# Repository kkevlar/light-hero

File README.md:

# light-hero

Fun work is in justin.c

`make rundemo`

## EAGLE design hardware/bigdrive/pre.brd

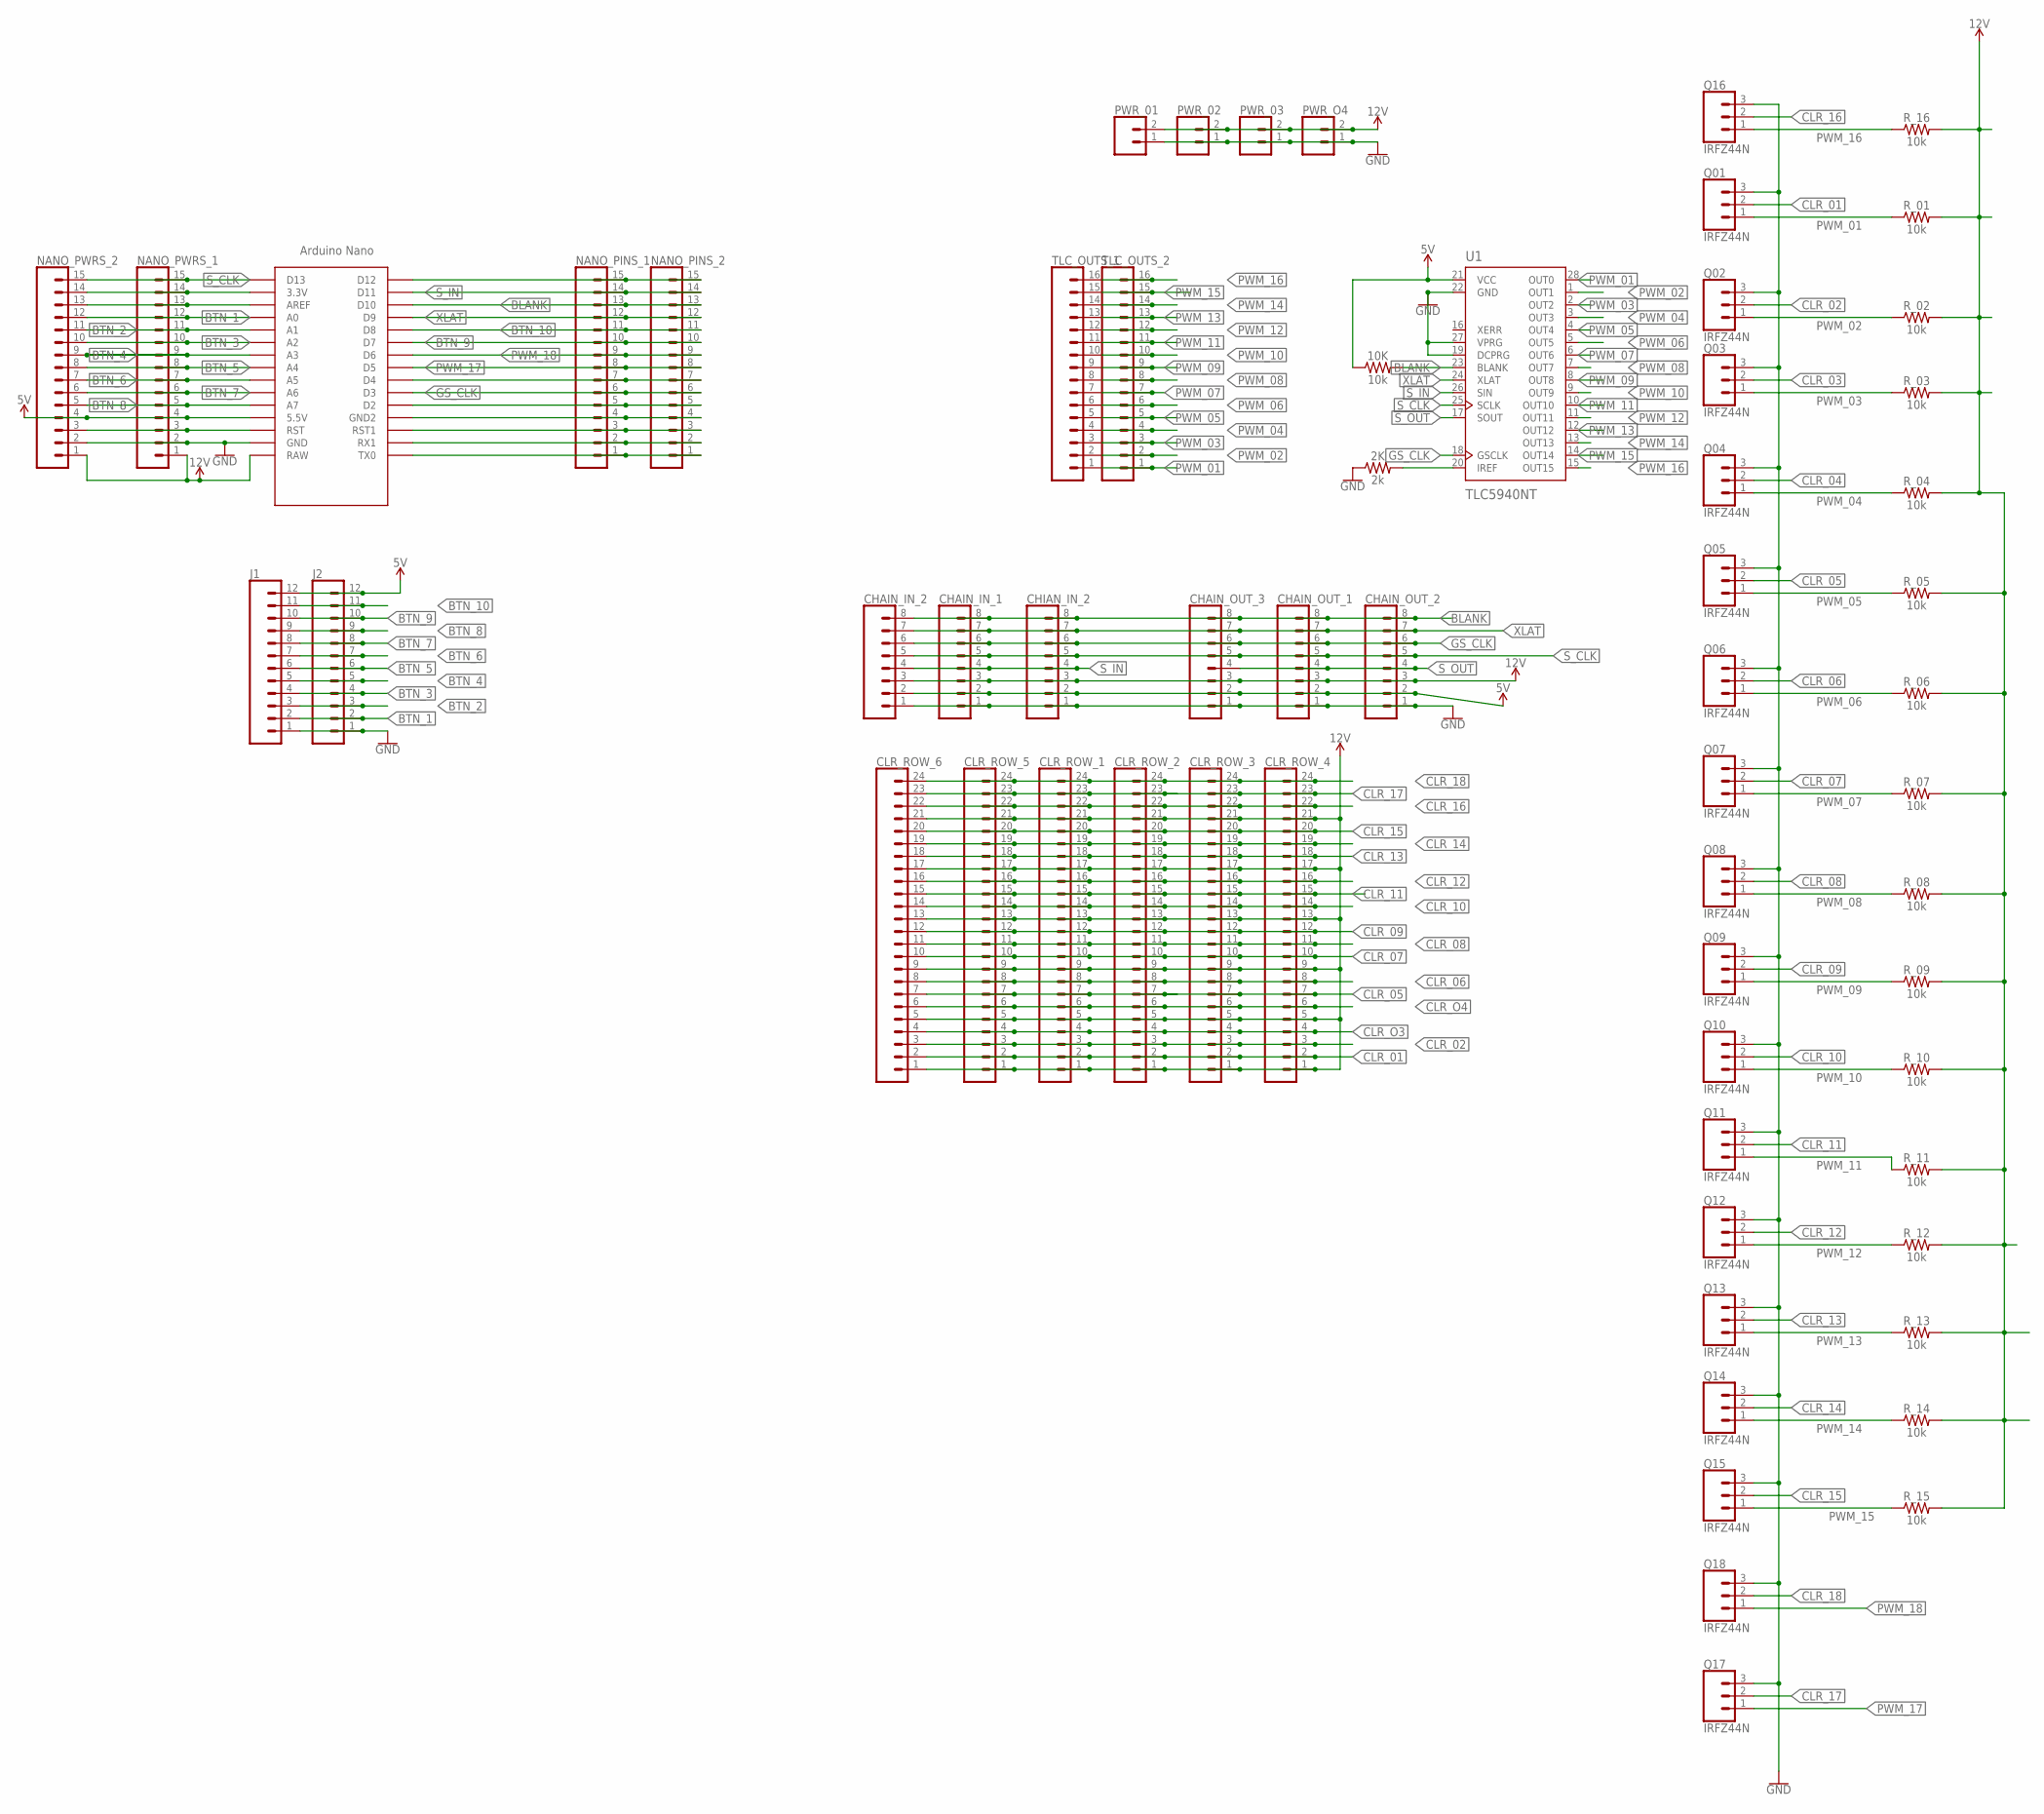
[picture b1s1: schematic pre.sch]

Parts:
2K: 2k; AXIAL-0.3
10K: 10k; AXIAL-0.3
CHAIN_IN_1, CHAIN_IN_2: CONN_08"; 1X08
CHAIN_OUT_1, CHAIN_OUT_2, CHAIN_OUT_3: CONN_08"; 1X08
CHIAN_IN_2: CONN_08"; 1X08
CLR_ROW_1, CLR_ROW_2, CLR_ROW_3, CLR_ROW_4, CLR_ROW_5, CLR_ROW_6: CONN_24; 1X24
J1, J2: CONN_12; 1X12
NANO_PINS_1, NANO_PINS_2: CONN_15; 1X15
NANO_PWRS_1, NANO_PWRS_2: CONN_15; 1X15
PWR_01, PWR_02: CONN_023.5MM; SCREWTERMINAL-3.5MM-2
PWR_03: CONN_02; 1X02
PWR_O4: CONN_02; 1X02
Q01, Q02, Q03, Q04, Q05, Q06, Q07, Q08, Q09, Q10, Q11, Q12, Q13, Q14, Q15, Q16, Q17, Q18: IRFZ44N; 1X03
R_01, R_02, R_03, R_04, R_05, R_06, R_07, R_08, R_09, R_10, R_11, R_12, R_13, R_14, R_15, R_16: 10k; AXIAL-0.3
TLC_OUTS_1, TLC_OUTS_2: CONN_16; 1X16
U1: TLC5940NT; DIL28-3
U$1: NANO

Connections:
5V: 10K.P$1 (1), CHAIN_IN_1.2, CHAIN_IN_2.2, CHAIN_OUT_1.2, CHAIN_OUT_2.2, CHAIN_OUT_3.2, CHIAN_IN_2.2, J1.12, J2.12, NANO_PWRS_1.4, NANO_PWRS_2.4, U1.21 (VCC), U$1.5V (5.5V)
12V: CHAIN_IN_1.3, CHAIN_IN_2.3, CHAIN_OUT_1.3, CHAIN_OUT_2.3, CHAIN_OUT_3.3, CHIAN_IN_2.3, CLR_ROW_1.1, CLR_ROW_1.5, CLR_ROW_1.9, CLR_ROW_1.13, CLR_ROW_1.17, CLR_ROW_1.21, CLR_ROW_2.1, CLR_ROW_2.5, CLR_ROW_2.9, CLR_ROW_2.13, CLR_ROW_2.17, CLR_ROW_2.21, CLR_ROW_3.1, CLR_ROW_3.5, CLR_ROW_3.9, CLR_ROW_3.13, CLR_ROW_3.17, CLR_ROW_3.21, CLR_ROW_4.1, CLR_ROW_4.5, CLR_ROW_4.9, CLR_ROW_4.13, CLR_ROW_4.17, CLR_ROW_4.21, CLR_ROW_5.1, CLR_ROW_5.5, CLR_ROW_5.9, CLR_ROW_5.13, CLR_ROW_5.17, CLR_ROW_5.21, CLR_ROW_6.1, CLR_ROW_6.5, CLR_ROW_6.9, CLR_ROW_6.13, CLR_ROW_6.17, CLR_ROW_6.21, NANO_PWRS_1.1, NANO_PWRS_2.1, PWR_01.2, PWR_02.2, PWR_03.2, PWR_O4.2, R_01.P$2 (2), R_02.P$2 (2), R_03.P$2 (2), R_04.P$2 (2), R_05.P$2 (2), R_06.P$2 (2), R_07.P$2 (2), R_08.P$2 (2), R_09.P$2 (2), R_10.P$2 (2), R_11.P$2 (2), R_12.P$2 (2), R_13.P$2 (2), R_14.P$2 (2), R_15.P$2 (2), R_16.P$2 (2), U$1.RAW
BLANK: 10K.P$2 (2), CHAIN_IN_1.8, CHAIN_IN_2.8, CHAIN_OUT_1.8, CHAIN_OUT_2.8, CHAIN_OUT_3.8, CHIAN_IN_2.8, NANO_PINS_1.13, NANO_PINS_2.13, U1.23 (BLANK), U$1.D10
BTN_1: J1.2, J2.2, NANO_PWRS_1.12, NANO_PWRS_2.12, U$1.A0
BTN_2: J1.3, J2.3, NANO_PWRS_1.11, NANO_PWRS_2.11, U$1.A1
BTN_3: J1.4, J2.4, NANO_PWRS_1.10, NANO_PWRS_2.10, U$1.A2
BTN_4: J1.5, J2.5, NANO_PWRS_1.9, NANO_PWRS_2.9, U$1.A3
BTN_5: J1.6, J2.6, NANO_PWRS_1.8, NANO_PWRS_2.8, U$1.A4
BTN_6: J1.7, J2.7, NANO_PWRS_1.7, NANO_PWRS_2.7, U$1.A5
BTN_7: J1.8, J2.8, NANO_PWRS_1.6, NANO_PWRS_2.6, U$1.A6
BTN_8: J1.9, J2.9, NANO_PWRS_1.5, NANO_PWRS_2.5, U$1.A7
BTN_9: J1.10, J2.10, NANO_PINS_1.10, NANO_PINS_2.10, U$1.D7
BTN_10: J1.11, J2.11, NANO_PINS_1.11, NANO_PINS_2.11, U$1.D8
CLR_01: CLR_ROW_1.2, CLR_ROW_2.2, CLR_ROW_3.2, CLR_ROW_4.2, CLR_ROW_5.2, CLR_ROW_6.2, Q01.2
CLR_02: CLR_ROW_1.3, CLR_ROW_2.3, CLR_ROW_3.3, CLR_ROW_4.3, CLR_ROW_5.3, CLR_ROW_6.3, Q02.2
CLR_03: Q03.2
CLR_04: Q04.2
CLR_05: CLR_ROW_1.7, CLR_ROW_2.7, CLR_ROW_3.7, CLR_ROW_4.7, CLR_ROW_5.7, CLR_ROW_6.7, Q05.2
CLR_06: CLR_ROW_1.8, CLR_ROW_2.8, CLR_ROW_3.8, CLR_ROW_4.8, CLR_ROW_5.8, CLR_ROW_6.8, Q06.2
CLR_07: CLR_ROW_1.10, CLR_ROW_2.10, CLR_ROW_3.10, CLR_ROW_4.10, CLR_ROW_5.10, CLR_ROW_6.10, Q07.2
CLR_08: CLR_ROW_1.11, CLR_ROW_2.11, CLR_ROW_3.11, CLR_ROW_4.11, CLR_ROW_5.11, CLR_ROW_6.11, Q08.2
CLR_09: CLR_ROW_1.12, CLR_ROW_2.12, CLR_ROW_3.12, CLR_ROW_4.12, CLR_ROW_5.12, CLR_ROW_6.12, Q09.2
CLR_10: CLR_ROW_1.14, CLR_ROW_2.14, CLR_ROW_3.14, CLR_ROW_4.14, CLR_ROW_5.14, CLR_ROW_6.14, Q10.2
CLR_11: CLR_ROW_1.15, CLR_ROW_2.15, CLR_ROW_3.15, CLR_ROW_4.15, CLR_ROW_5.15, CLR_ROW_6.15, Q11.2
CLR_12: CLR_ROW_1.16, CLR_ROW_2.16, CLR_ROW_3.16, CLR_ROW_4.16, CLR_ROW_5.16, CLR_ROW_6.16, Q12.2
CLR_13: CLR_ROW_1.18, CLR_ROW_2.18, CLR_ROW_3.18, CLR_ROW_4.18, CLR_ROW_5.18, CLR_ROW_6.18, Q13.2
CLR_14: CLR_ROW_1.19, CLR_ROW_2.19, CLR_ROW_3.19, CLR_ROW_4.19, CLR_ROW_5.19, CLR_ROW_6.19, Q14.2
CLR_15: CLR_ROW_1.20, CLR_ROW_2.20, CLR_ROW_3.20, CLR_ROW_4.20, CLR_ROW_5.20, CLR_ROW_6.20, Q15.2
CLR_16: CLR_ROW_1.22, CLR_ROW_2.22, CLR_ROW_3.22, CLR_ROW_4.22, CLR_ROW_5.22, CLR_ROW_6.22, Q16.2
CLR_17: CLR_ROW_1.23, CLR_ROW_2.23, CLR_ROW_3.23, CLR_ROW_4.23, CLR_ROW_5.23, CLR_ROW_6.23, Q17.2
CLR_18: CLR_ROW_1.24, CLR_ROW_2.24, CLR_ROW_3.24, CLR_ROW_4.24, CLR_ROW_5.24, CLR_ROW_6.24, Q18.2
CLR_O3: CLR_ROW_1.4, CLR_ROW_2.4, CLR_ROW_3.4, CLR_ROW_4.4, CLR_ROW_5.4, CLR_ROW_6.4
CLR_O4: CLR_ROW_1.6, CLR_ROW_2.6, CLR_ROW_3.6, CLR_ROW_4.6, CLR_ROW_5.6, CLR_ROW_6.6
GND: 2K.P$1 (1), CHAIN_IN_1.1, CHAIN_IN_2.1, CHAIN_OUT_1.1, CHAIN_OUT_2.1, CHAIN_OUT_3.1, CHIAN_IN_2.1, J1.1, J2.1, NANO_PINS_1.4, NANO_PINS_2.4, NANO_PWRS_1.2, NANO_PWRS_2.2, PWR_01.1, PWR_02.1, PWR_03.1, PWR_O4.1, Q01.3, Q02.3, Q03.3, Q04.3, Q05.3, Q06.3, Q07.3, Q08.3, Q09.3, Q10.3, Q11.3, Q12.3, Q13.3, Q14.3, Q15.3, Q16.3, Q17.3, Q18.3, U1.19 (DCPRG), U1.22 (GND), U1.27 (VPRG), U$1.GND, U$1.GND1 (GND2)
GS_CLK: CHAIN_IN_1.6, CHAIN_IN_2.6, CHAIN_OUT_1.6, CHAIN_OUT_2.6, CHAIN_OUT_3.6, CHIAN_IN_2.6, NANO_PINS_1.6, NANO_PINS_2.6, U1.18 (GSCLK), U$1.D3
unnamed: 2K.P$2 (2), U1.20 (IREF)
unnamed: NANO_PWRS_1.14, NANO_PWRS_2.14, U$1.3.3V
unnamed: NANO_PWRS_1.13, NANO_PWRS_2.13, U$1.AREF
unnamed: NANO_PWRS_1.3, NANO_PWRS_2.3, U$1.RST
unnamed: NANO_PINS_1.15, NANO_PINS_2.15, U$1.D12
unnamed: NANO_PINS_1.3, NANO_PINS_2.3, U$1.RST1
unnamed: NANO_PINS_1.2, NANO_PINS_2.2, U$1.RX1
unnamed: NANO_PINS_1.7, NANO_PINS_2.7, U$1.D4
unnamed: NANO_PINS_1.1, NANO_PINS_2.1, U$1.TX0
unnamed: NANO_PINS_1.5, NANO_PINS_2.5, U$1.D2
PWM_01: Q01.1, R_01.P$1 (1), TLC_OUTS_1.1, TLC_OUTS_2.1, U1.28 (OUT0)
PWM_02: Q02.1, R_02.P$1 (1), TLC_OUTS_1.2, TLC_OUTS_2.2, U1.1 (OUT1)
PWM_03: Q03.1, R_03.P$1 (1), TLC_OUTS_1.3, TLC_OUTS_2.3, U1.2 (OUT2)
PWM_04: Q04.1, R_04.P$1 (1), TLC_OUTS_1.4, TLC_OUTS_2.4, U1.3 (OUT3)
PWM_05: Q05.1, R_05.P$1 (1), TLC_OUTS_1.5, TLC_OUTS_2.5, U1.4 (OUT4)
PWM_06: Q06.1, R_06.P$1 (1), TLC_OUTS_1.6, TLC_OUTS_2.6, U1.5 (OUT5)
PWM_07: Q07.1, R_07.P$1 (1), TLC_OUTS_1.7, TLC_OUTS_2.7, U1.6 (OUT6)
PWM_08: Q08.1, R_08.P$1 (1), TLC_OUTS_1.8, TLC_OUTS_2.8, U1.7 (OUT7)
PWM_09: Q09.1, R_09.P$1 (1), TLC_OUTS_1.9, TLC_OUTS_2.9, U1.8 (OUT8)
PWM_10: Q10.1, R_10.P$1 (1), TLC_OUTS_1.10, TLC_OUTS_2.10, U1.9 (OUT9)
PWM_11: Q11.1, R_11.P$1 (1), TLC_OUTS_1.11, TLC_OUTS_2.11, U1.10 (OUT10)
PWM_12: Q12.1, R_12.P$1 (1), TLC_OUTS_1.12, TLC_OUTS_2.12, U1.11 (OUT11)
PWM_13: Q13.1, R_13.P$1 (1), TLC_OUTS_1.13, TLC_OUTS_2.13, U1.12 (OUT12)
PWM_14: Q14.1, R_14.P$1 (1), TLC_OUTS_1.14, TLC_OUTS_2.14, U1.13 (OUT13)
PWM_15: Q15.1, R_15.P$1 (1), TLC_OUTS_1.15, TLC_OUTS_2.15, U1.14 (OUT14)
PWM_16: Q16.1, R_16.P$1 (1), TLC_OUTS_1.16, TLC_OUTS_2.16, U1.15 (OUT15)
PWM_17: NANO_PINS_1.8, NANO_PINS_2.8, Q17.1, U$1.D5
PWM_18: NANO_PINS_1.9, NANO_PINS_2.9, Q18.1, U$1.D6
S_CLK: CHAIN_IN_1.5, CHAIN_IN_2.5, CHAIN_OUT_1.5, CHAIN_OUT_2.5, CHAIN_OUT_3.5, CHIAN_IN_2.5, NANO_PWRS_1.15, NANO_PWRS_2.15, U1.25 (SCLK), U$1.D13
S_IN: CHAIN_IN_1.4, CHAIN_IN_2.4, CHIAN_IN_2.4, NANO_PINS_1.14, NANO_PINS_2.14, U1.26 (SIN), U$1.D11
S_OUT: CHAIN_OUT_1.4, CHAIN_OUT_2.4, CHAIN_OUT_3.4, U1.17 (SOUT)
XLAT: CHAIN_IN_1.7, CHAIN_IN_2.7, CHAIN_OUT_1.7, CHAIN_OUT_2.7, CHAIN_OUT_3.7, CHIAN_IN_2.7, NANO_PINS_1.12, NANO_PINS_2.12, U1.24 (XLAT), U$1.D9

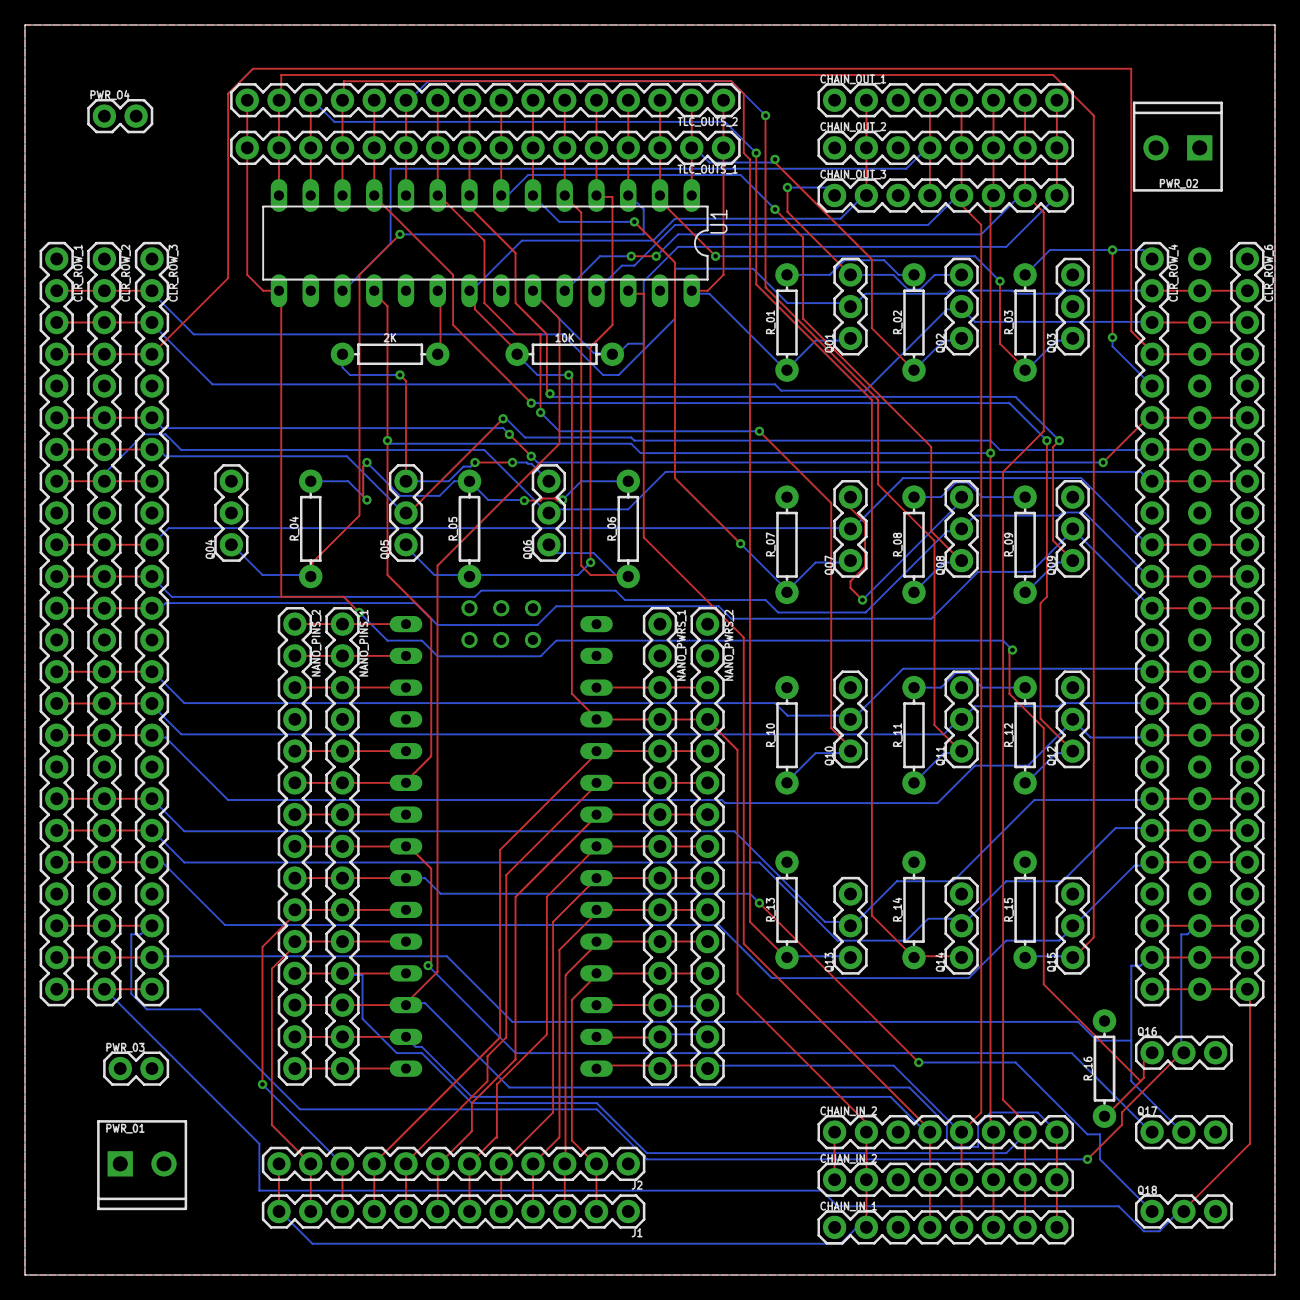
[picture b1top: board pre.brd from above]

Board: 2 copper layers, 100.0 x 100.0 mm, 62 parts (1 on the bottom side), 65 nets.

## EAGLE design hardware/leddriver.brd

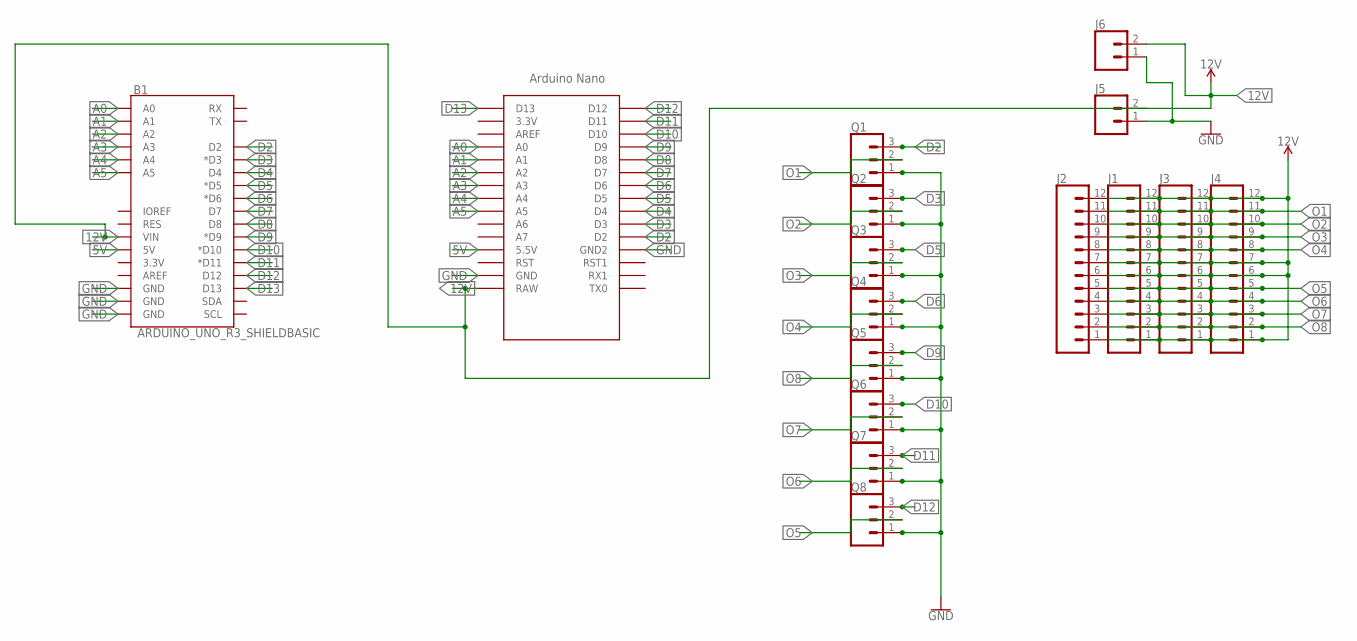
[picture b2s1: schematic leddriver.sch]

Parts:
B1: ARDUINO_UNO_R3_SHIELDBASIC; UNO_R3_SHIELD
J1, J2, J3, J4: CONN_12; 1X12
J5, J6: CONN_02; 1X02
Q1, Q2, Q3, Q4, Q5, Q6, Q7, Q8: 455-1750-1-ND; 1X03
U$1: NANO

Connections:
5V: B1.5V, U$1.5V (5.5V)
12V: B1.VIN, J1.1, J1.6, J1.7, J1.12, J2.1, J2.6, J2.7, J2.12, J3.1, J3.6, J3.7, J3.12, J4.1, J4.6, J4.7, J4.12, J5.2, J6.2, U$1.RAW
A0: B1.A0, U$1.A0
A1: B1.A1, U$1.A1
A2: B1.A2, U$1.A2
A3: B1.A3, U$1.A3
A4: B1.A4, U$1.A4
A5: B1.A5, U$1.A5
D2: B1.D2, Q1.3, U$1.D2
D3: B1.D3 (*D3), Q2.3, U$1.D3
D4: B1.D4, U$1.D4
D5: B1.D5 (*D5), Q3.3, U$1.D5
D6: B1.D6 (*D6), Q4.3, U$1.D6
D7: B1.D7, U$1.D7
D8: B1.D8, U$1.D8
D9: B1.D9 (*D9), Q5.3, U$1.D9
D10: B1.D10 (*D10), Q6.3, U$1.D10
D11: B1.D11 (*D11), Q7.3, U$1.D11
D12: B1.D12, Q8.3, U$1.D12
D13: B1.D13, U$1.D13
GND: B1.GND@0 (GND), B1.GND@1 (GND), B1.GND@2 (GND), J5.1, J6.1, Q1.1, Q2.1, Q3.1, Q4.1, Q5.1, Q6.1, Q7.1, Q8.1, U$1.GND, U$1.GND1 (GND2)
O1: J1.11, J2.11, J3.11, J4.11, Q1.2
O2: J1.10, J2.10, J3.10, J4.10, Q2.2
O3: J1.9, J2.9, J3.9, J4.9, Q3.2
O4: J1.8, J2.8, J3.8, J4.8, Q4.2
O5: J1.5, J2.5, J3.5, J4.5, Q8.2
O6: J1.4, J2.4, J3.4, J4.4, Q7.2
O7: J1.3, J2.3, J3.3, J4.3, Q6.2
O8: J1.2, J2.2, J3.2, J4.2, Q5.2

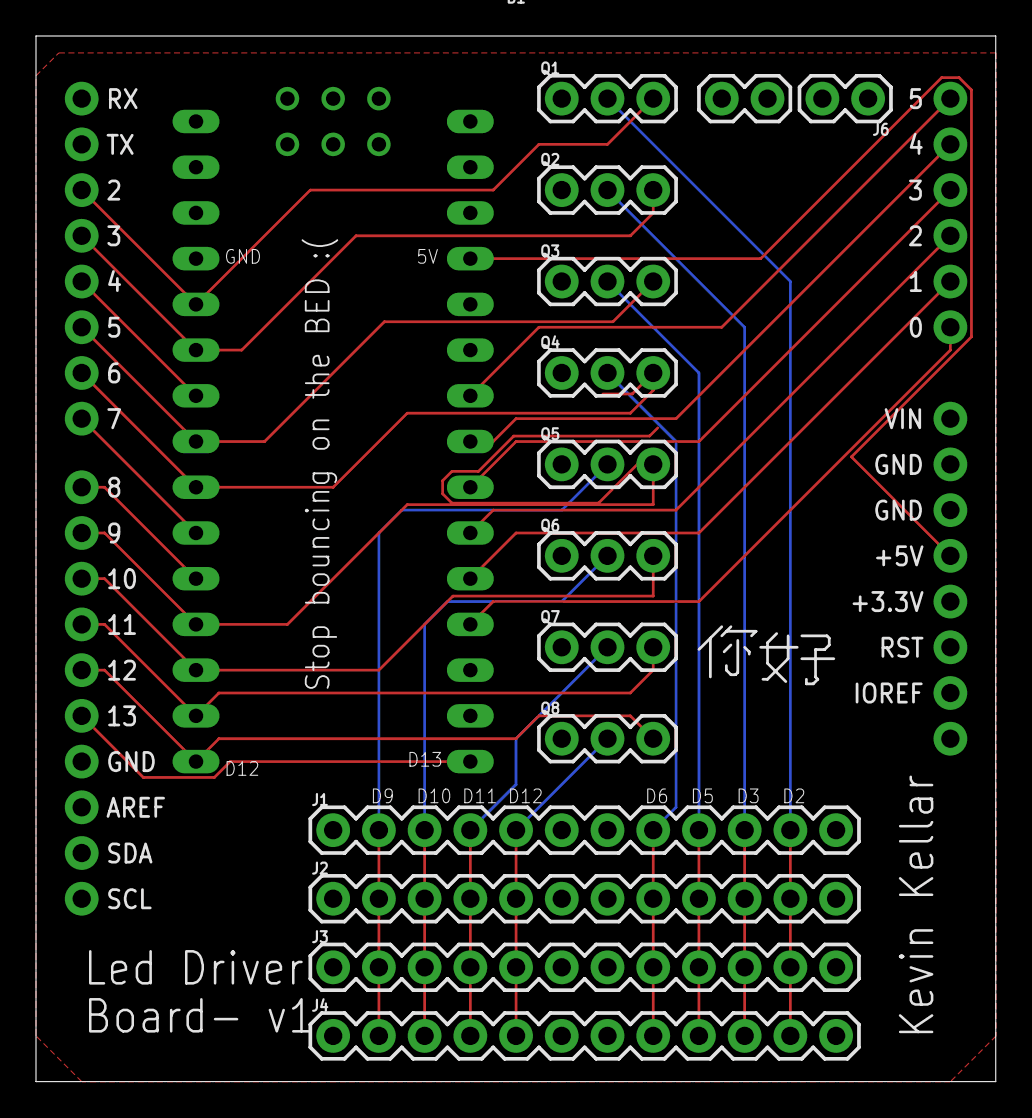
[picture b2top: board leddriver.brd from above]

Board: 2 copper layers, 53.3 x 58.1 mm, 16 parts (0 on the bottom side), 29 nets.

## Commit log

2018-10-29 initial commit :)
2018-10-30 woo the java front end
2018-10-30 added to gitignore
2018-10-30 it refresh properly
2018-10-31 added ino and ino to makefile
2018-10-31 added a test program
2018-10-31 hehe
2018-10-31 now it actually makes
2018-10-31 added strips instead
2018-10-31 nano folder into gitignore
2018-10-31 SUPER MESSY ALERT
2018-10-31 woo justin.c
2018-10-31 instructions in readme
2018-11-01 compiles ino but is super super ugly makefile
2018-11-02 thigns
2018-11-02 made
2018-11-02 justin's in town
2018-11-02 made ms function
2018-11-02 added sec_per_beat functio
2018-11-02 fixed syntax errors
2018-11-02 busted
2018-11-02 now we'll be able to supply a bpm and have the lights be entirely dependent on the tempo we provide
2018-11-03 taking Ls left and right
2018-11-04 its goooood
2018-11-04 now you can sleep beats based on a supplied bpm; should make everything a lot simpler
2018-11-04 simplified logic
2018-11-05 changed refresh rate
2018-11-16 script things
2018-11-16 script things2
2018-11-16 ok huge dub shouldnt lag now
2018-11-18 justin.c edited
2018-12-31 woooooo they mostly work irl
2018-12-31 added a swap sides
2019-01-01 partial pulse useless
2019-03-11 ug im so mad
2019-03-13 makes using ardmakefile instead
2019-03-13 fun to play
2019-03-14 added hardware
2019-03-16 bigdrive
2019-03-17 aaaa
2020-03-26 added quickcubes
2020-03-26 heck yeah
2020-03-27 they now light up eachother
2020-03-27 generated summerair
2020-03-27 made a simple transpose
2020-03-28 living the cpp dream
2020-03-28 can do playback
2020-03-29 able to start and restart playback with spacebar
2020-03-29 addasfsdfa

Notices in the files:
parts and their libraries:
SparkFun-Resistors: Licensing: Creative Commons ShareAlike 4.0 International - https://creativecommons.org/licenses/by-sa/4.0
